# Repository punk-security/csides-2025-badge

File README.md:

# This is the repo for the CSIDES 2025 crab badge

**This badge is a litle bit funky as we ported the TV-B-GONE code to this badge so you cna use it to turn off most TVs**

This is our most complex badge to date, with quite a few extra components. Soldering it is not easy.

The badge is printed with full-colour UV printed silkscreen. Usually we use JLCPCB for this (and to be honest they're quality is better in our opinion) but they cant print full-colour onto a HASL (silver) finished board. They can only do it with ENIG, which is the gold look. As this crab is meant to be a cyborg, we had to go with PCBWAY this time. 

As with other badges, we made the first design in AutoCAD EAGLE. It's just easy to use, and we're really familiar with it. Then we export it as a gerber and include the silkscreen file manually. This is then provided to PCBWAY. That gerber is in this repo, so you can skip all that.

### TV-B-GONE

For a long time, we've wanted to do a badge which can turn TVs off. A cybord crab, with it's little eye stalk things seemed like our perfect opportunity. It took a lot of work to get the code to work, and tweak the circuitry to get a good range.

Go check out the original code - https://github.com/shirriff/Arduino-TV-B-Gone  
... and the main website- https://www.tvbgone.com/  
... and this instructables - https://www.instructables.com/4-DIY-TV-B-Gone/  
... and this one - https://www.instructables.com/350-DIY-TV-B-Gone-Mico/

We really stood on the shoulders of giants with this, and hopefully added a new and interesting twist. The range is pretty good thanks to a capacitor, which is loosely optimised through trial and error. Essentially you want it to charge as as quickly as possible to not impact the microcontroller, but not discharge completely during a signal transmission. Also size / cost etc.

The badge has a potentiometer so you can control the resistance to the LEDs, and therefore limit their current draw. On fresh batteries, you can go full power and get 20-25m of range. As the batteries run low, the badge will keep crashing as you try to transmit so just tweak the pot.

Lots of things in this repo:

- EAGLE.brd: The AutoCAD Eagle board design
- EAGLE.sch: The AutoCAD Eagle circuit schematic
- gerber.zip: the file you can upload to JLCPCB and order your own badge, as is
- SILK_TOP.png: the full colour silkscreen print
- firmware.ino: the arduino code that powers the badge, which you can modify and flash via the SAO connector
- main.h: This is part of the TV-B-GONE code we ported
- WORLD_IR_CODES.h: More of the TV-B-GONE code

## Bill Of Materials

There are a lot of components with this badge. It started out on a breadboard and we tried to keep the part count as low as possible whilst making it actually work! The transistors are a right pain to solder!

This is our first badge using a 1614 microcontroller too. We couldn't fit the code onto the usual ATTINY412.

Essentially its:

* ATTINY1614 microcontroller
* Button - any surface mount button fitting the footprint will work
* NC Button - The reset button it the same footprint as the usual button, but is "open" when pressed. You can skip this and just solder the pads together if you prefer.
* CR2032 battery clip x 2 - surface mount not through hole
* Neopixel 5050 addressable LED - Definitely get the right version of these
* 100 Ohm Trimmer - TC33X-2-101E
* Aishi 100uF Cap - EMK0JM101E83D00R
* NPN transistor SOT-23 - MMBT3904
* 940nm IR LEDS - We had 2 different ones - 10 degree and 40 degree transmission beams

## How does it work?

The badge does the usually blinky modes, but also turns TV off.

To cycle flashy modes, you just short press the button on the badge. 

It can also turn TVs off. To do this, hold the button in for around 3 or 4 seconds and then loose. The badge will start flashing green in one LED. Every LED flash is another European TV off code. When its run out of codes, it will start flashing blue. These are the US codes. When its run out of those, it will return to normally flashy mode. You can exit early at any point by simply pressing the button again.

Holding the button in for a long time will cause the badge to go to sleep. It will do this itself after 60 mins-ish.

## Ordering your own badge

We've uploaded the AutoCAD EAGLE schematic and board design!  You will probably have to do some tweaks to get it working as they're not designed to be standalone exports.

We've also uploaded the gerber.zip.  Take this to PCBWAY and you can order your own exact copies of the board :)

## Writing and flashing code!

We use [MegaTinyCore](https://github.com/SpenceKonde/megaTinyCore) for the arduino interface.

Dev and flashing is done within the Arduino IDE ( < v2 ) using a jtag2updi interface, as discussed [here](https://github.com/SpenceKonde/AVR-Guidance/blob/master/UPDI/jtag2updi.md)

We use [these little usb sticks](https://amzn.eu/d/c0lx0wG), with a 4.7k resistor soldered between the Tx and Rx lines.  

### Installing MegaTinyCore dependencies

This board package can be installed via the board manager in arduino. The boards manager URL is:

`http://drazzy.com/package_drazzy.com_index.json`

1. File -> Preferences, enter the above URL in "Additional Boards Manager URLs"
2. Tools -> Boards -> Boards Manager...
3. Wait while the list loads (takes longer than one would expect, and refreshes several times).
4. Select "megaTinyCore by Spence Konde" and click "Install". For best results, choose the most recent version.

### Setting up the IDE

1. Open the file **firmware.ino** in arduino
2. Select tools > Board > megaTinyCore > ATtiny412/402/212/202
3. Select tools > Chip > ATtiny412
4. Select tools > Clock > 16Mhz internal *(it wont turn off TVs otherwise)*
5. Select tools > Programmer > SerialUPDI SLOW
6. Select tools > Port > ( pick your COM port)

### Flashing firmware
1. Connect the 3v3 pin to 3v on your usb (maybe wedge it in the battery clip)
2. Connect GND to GND
3. Connect UPDI to the RxD port
4. Click Upload button

## How to solder?

It's super tricky!

Essentially, line up the parts and solder them.

We placed the ATTINY1614 on the front as it looked quite cool. It's horrible to solder. Line up the micontroller dimple with the circle, and try not to bridge the pins with the crabs metal background. 

The back is also tricky. Most parts are obvious. The RST button should be a normally closed button, or just solder a bit of wire in its place. The triangles near the LED placements show you how to rotate the LEDs into position.

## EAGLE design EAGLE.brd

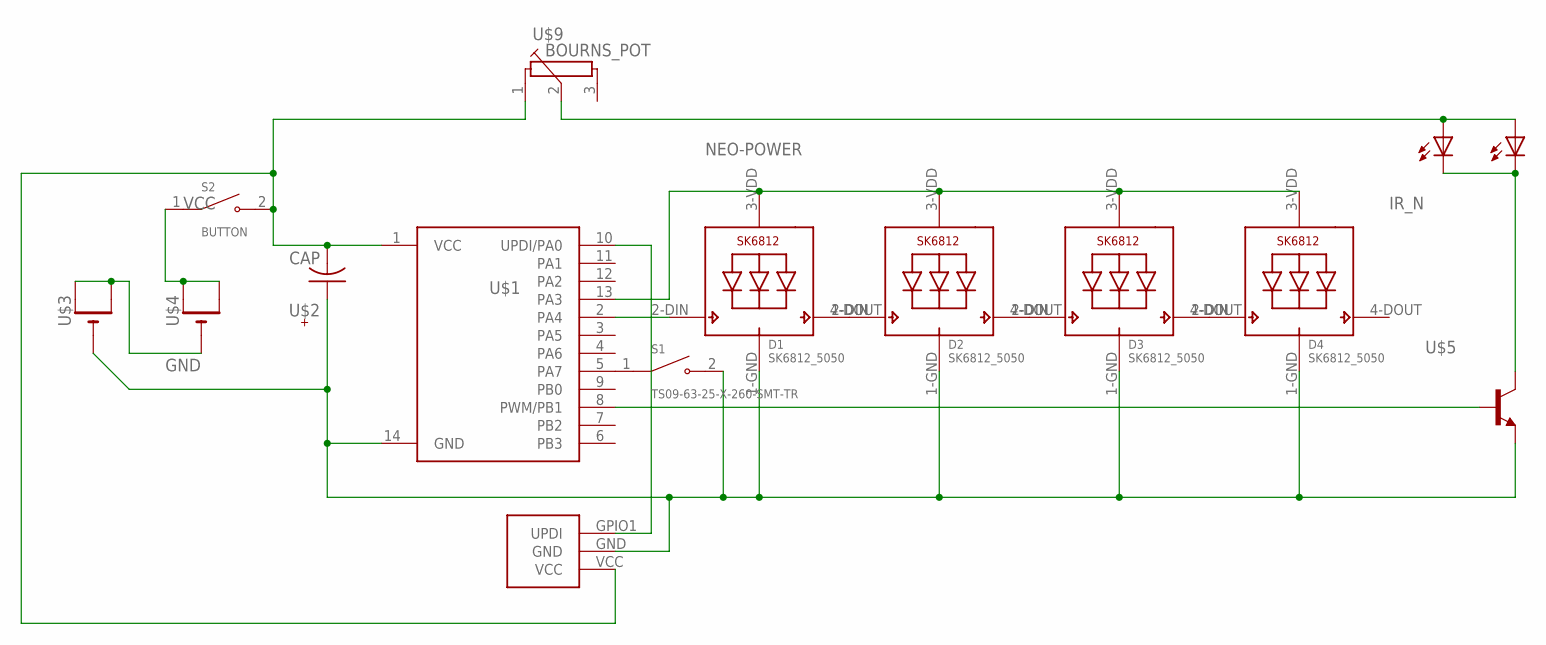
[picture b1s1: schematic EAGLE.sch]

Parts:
D1, D2, D3, D4: SK6812_5050; SK6812_REVERSE_W_CUT
S1: TS09-63-25-X-260-SMT-TR; SW_TS09-63-25-X-260-SMT-TR
S2: BUTTON; SW_TS09-63-25-X-260-SMT-TR
U$1: ATTINY1614ATTINY1614; SO14
U$2: CAP; UD-6,3X5,8_NICHICON
U$3, U$4: CR2032SMT; CR2032-SMD
U$5: NPN; SOT23
U$6, U$7: LEDSIDESOLDER; LED3MM_5MM_SIDESOLDER
U$8: SAO; SAO_SMD
U$9: BOURNS_POT; 3223W

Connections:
GND: D1.1-GND (GND), D2.1-GND (GND), D3.1-GND (GND), D4.1-GND (GND), S1.2, U$1.14 (GND), U$2.+, U$3.GND, U$5.2 (E), U$8.GND
IR_N: U$5.3 (C), U$6.KN (C), U$7.KN (C)
IR_PWR: U$6.AN (A), U$7.AN (A), U$9.2 (1S)
unnamed: S1.1, U$1.5 (PA7)
unnamed: D1.4-DOUT (DO), D2.2-DIN (DI)
unnamed: D2.4-DOUT (DO), D3.2-DIN (DI)
unnamed: D3.4-DOUT (DO), D4.2-DIN (DI)
unnamed: S2.1, U$4.+$1 (+), U$4.+$2 (+1)
unnamed: U$3.+$1 (+), U$3.+$2 (+1), U$4.GND
NEO-POWER: D1.3-VDD (VDD), D2.3-VDD (VDD), D3.3-VDD (VDD), D4.3-VDD (VDD), U$1.13 (PA3)
NEO_SIGNAL: D1.2-DIN (DI), U$1.2 (PA4)
PWM: U$1.8 (PWM/PB1), U$5.1 (B)
UPDI: U$1.10 (UPDI/PA0), U$8.GPIO1 (UPDI)
VCC: S2.2, U$1.1 (VCC), U$2.-, U$8.VCC, U$9.1 (1A)

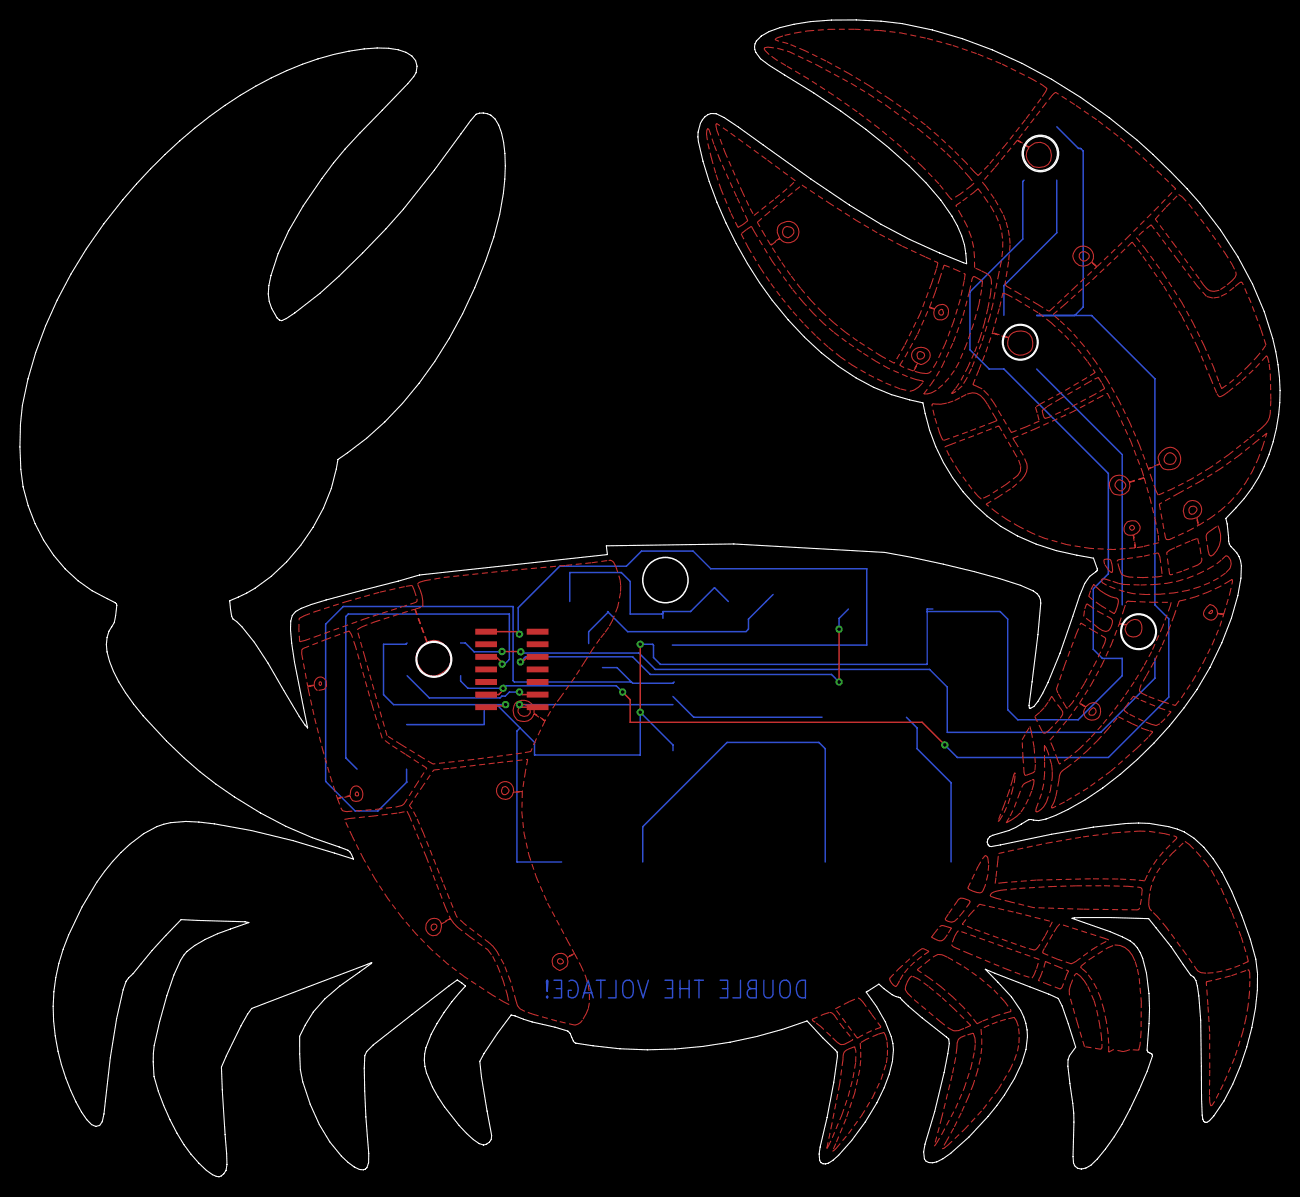
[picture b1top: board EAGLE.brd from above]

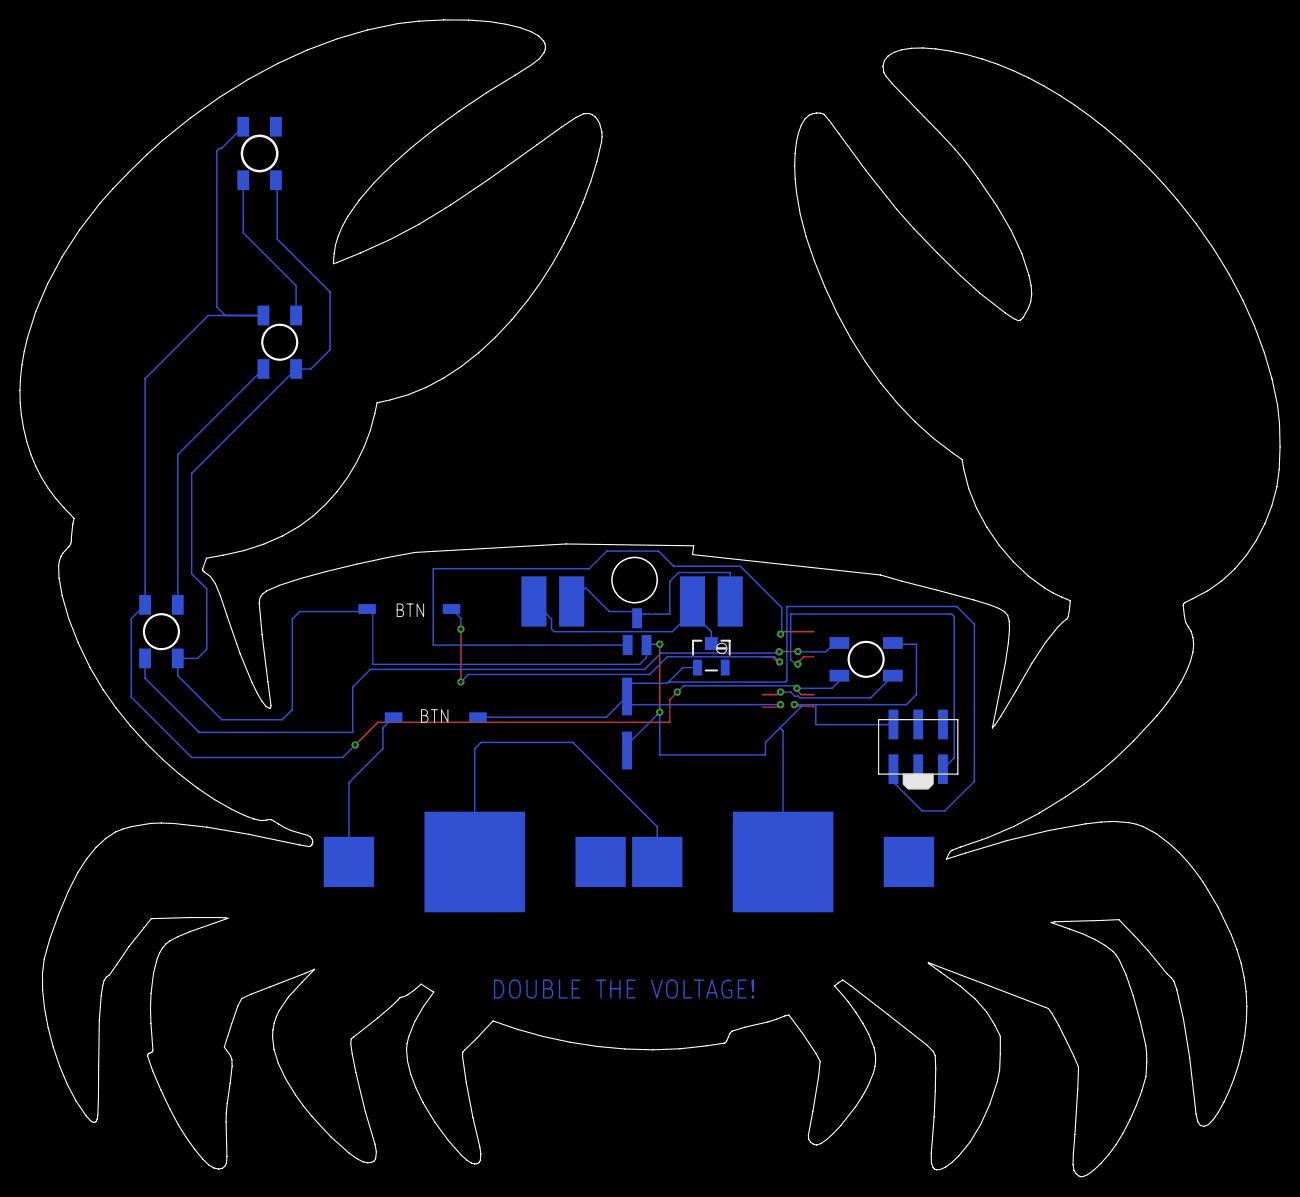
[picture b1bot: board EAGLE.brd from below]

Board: 2 copper layers, 127.2 x 116.8 mm, 15 parts (14 on the bottom side), 14 nets.

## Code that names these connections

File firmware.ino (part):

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// ==== CONFIGURATION ====

// Pin definitions
#define IRLED_PIN   PIN_PB1  // TCA0 WO1
#define TRIGGER_PIN PIN_PA7
#define NEOPIXEL_DATA PIN_PA4
#define NEOPIXEL_PWR PIN_PA3


# define WAKE_TIME_MS 2700000 // 60 mins
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
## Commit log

2025-11-02 init
2025-11-02 typo
